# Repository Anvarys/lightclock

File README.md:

<div align="center">
  
</div>

<h2 align="center">Light Clock</h2>
<p align="center">
A custom PCB-based Clock/Alarm with a runrise alarm, a circle of capacitive touch controls to easily choose the time and a 2.42" OLED display
</p>

## About the project

A custom PCB-based Clock/Alarm with a 3d printed enclosure. It features a runrise alarm option (72 LEDs), a 2.42" OLED display, many capacitive touch controls (24 around in a circle and 4 for the main controls) and a buzzer.

I made this project because I wanted to have a runrise alarm to wake up more naturally and also be easy to set up alarms with few clicks and without any additional installation required.

## Light Clock's features in more detail

### Sunrise alarm & LEDs

Light Clock has a runsrise type of alarm, which will slowly rise the luminosity up to a set time for you to wake up naturally, like with a real sunrise. This can be calibrated, meaning you can set up a test alarm on a day you don't need to wake up at a certain time and see at which luminosity you will wake up. There is also a buzzer (the shaky circle on the simplified design picture) to wake you up with it, just in case, as you might not wake up from the light.

It uses 72LEDs with 3000K warm lighting, with a total maximum luminosity flux of over 2000 lumens. They can also be lighten up in individual groups of 3, so a total of 24 groups is present, to show the current time using those same LEDs but dimmed, also as it has 24 groups it can do both 24 and 12 sections for the time, which you can choose as you prefer.

### Capacitive touch controls

This project has a total of 28 capacitive touch sensors (you can identify all of them on the simplified design picture as the ones having unclear borders), they were made by placing pads on the PCB and using ICs to measure precise capacitance values. 

4 of them are used to control the menu: 2 arrows for navigating between options and change values, a circle to select an option and a square be used as a return button.

And the other 24 are distributed evenly in a circle next to the LEDs, they will be used to easily choose time of your alarm or change number variables. For example if you need to setup an alarm for 10:15am you can simply click the 10th pad counting clockwise from the top to set the hour, and then click on 7th pad to set the minutes.

### Display

The display is a 2.42" OLED display from Waveshare. It has a resolution of 128x64, which is not detailed, but very sufficent for pixeled fonts and interfaces. It will display the time in the format you prefer, and it can be set into a "show on touch" mode, so that the display would be off by default but when you touch any capacitive touch sensor it will show the time for a certain period of time.

### Other

It also has an RTC clock with a coin battery to sustain precise time for months, while the battery is not required it is very recommended as then if you power off the clock you won't need to set up the time again each time.

Since the LEDs and ICs produce heat there is a 40x40x7mm fan on the back which is very quiet, so should not be a worry that it might be disturbing.

Also I added 4 exposed GPIO pads on the PCB that you can use them to integrate something extra to this device if you want to.

## How to build your own light clock

First you would want to buy all the required components found in the [BOM](https://github.com/Anvarys/lightclock/blob/main/BOM/BOM.csv), order the pcb using the gerbers from the [production folder](https://github.com/Anvarys/lightclock/tree/main/PCB/production) (you can also find the positions file which is required for JLCPCB to solder components for you, which is also an option). Then you will need to solder everything by looking at the [schematic](https://github.com/Anvarys/lightclock/blob/main/images/schematic.pdf) for references of the components. Also you will need to 3d print the enclosure, files of which you can find in the [CAD folder](https://github.com/Anvarys/lightclock/tree/main/CAD). Now you will need to flash the device with the [firmware](https://github.com/Anvarys/lightclock/tree/main/firmware) using [VS code](https://code.visualstudio.com) with [PlatformIO](https://platformio.org). Then when you check that it boots up successfully you can assemble the enclosure by first mounting the fan on the back enclosure part, then mounting the pcb to it as well, and finally snap the front enclosure part on the PCB.

## Schematic

## PCB

3D renders:

<table><tr>
<td></td>
<td></td>
</tr></table>

## Assembly

## Assembled

<table><tr>
<td></td>
<td></td>
</tr></table>

## Tools I used

<ul style="list-style-type:none;">
  <li>PCB design: <a href="https://kicad.org">KiCAD</a></li>
  <li>3D design: <a href="https://www.autodesk.com/products/fusion-360/overview">Autodesk Fusion</a> (free version)</li>
  <li>Firmware: <a href="https://code.visualstudio.com">VS code</a> with <a href="https://platformio.org">PlatformIO</a></li>
  <li>Art: <a href="https://figma.com">Figma</a></li>
</ul>

## BOM

Totals
| | |
|-|-|
|Parts|102.84$|
|Supplies|22.08$|
|Shipping|39.34$|
|Everything|164.26$|

You can find the detailed BOM in [/BOM](https://github.com/Anvarys/lightclock/tree/main/BOM)

P.S. I had to choose fast shipping or amazon instead of aliexpress as otherwise I won't be able to build the project until August

## Repository structure

- [/CAD](https://github.com/Anvarys/lightclock/tree/main/CAD) - All the 3d models and the assembly
- [/PCB](https://github.com/Anvarys/lightclock/tree/main/PCB) - KiCAD PCB project
  - [/production](https://github.com/Anvarys/lightclock/tree/main/PCB/production) - Files required to produce the PCB (and PCBA for JLCPCB)
  - [/scripts](https://github.com/Anvarys/lightclock/tree/main/PCB/scripts) - Scripts I made in python to place the LEDs and capacitive touch pad footprints perfectly on the PCB
- [/firmware](https://github.com/Anvarys/lightclock/tree/main/firmware) - PlatformIO project with all firmware sources and configs
- [/BOM](https://github.com/Anvarys/lightclock/tree/main/BOM) - Bill of materials (the list of all parts you need to buy)
- [/images](https://github.com/Anvarys/lightclock/tree/main/images) - Images of the project such as 3d renders, schematic, PCB, zine, etc.

## Zine

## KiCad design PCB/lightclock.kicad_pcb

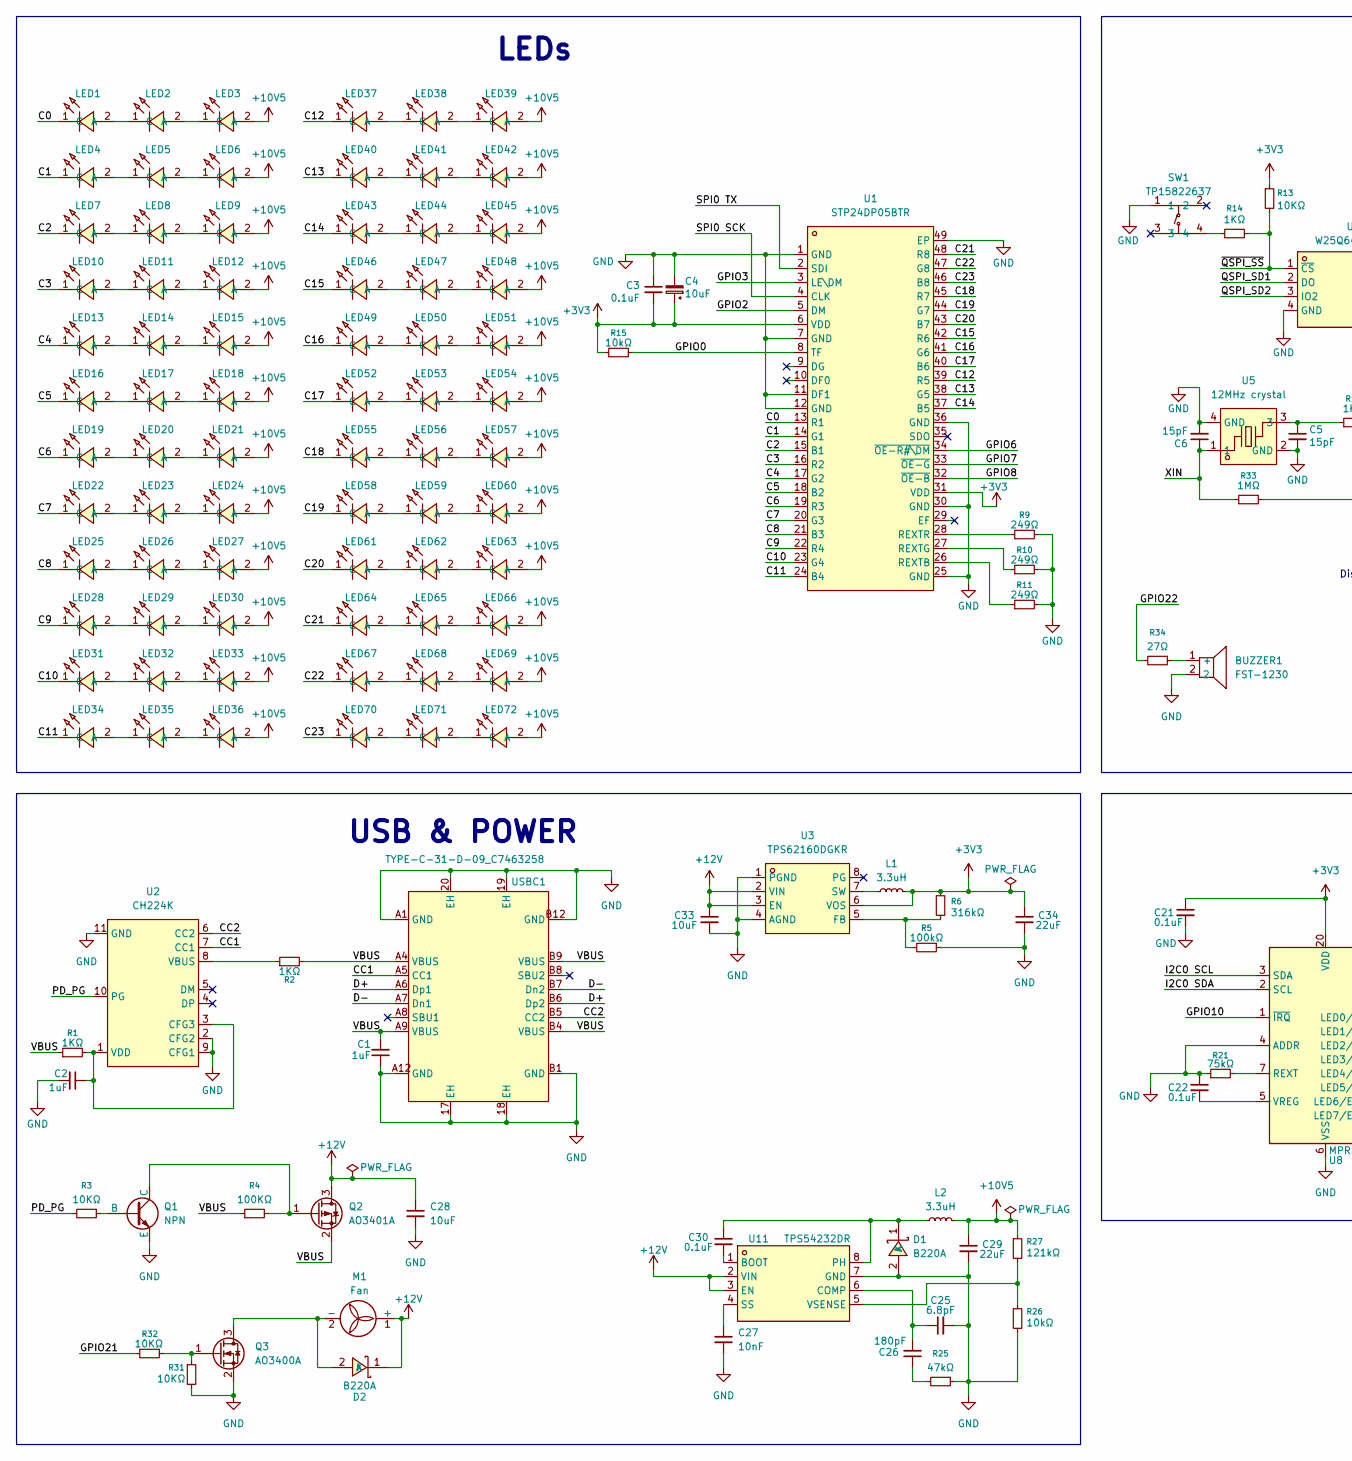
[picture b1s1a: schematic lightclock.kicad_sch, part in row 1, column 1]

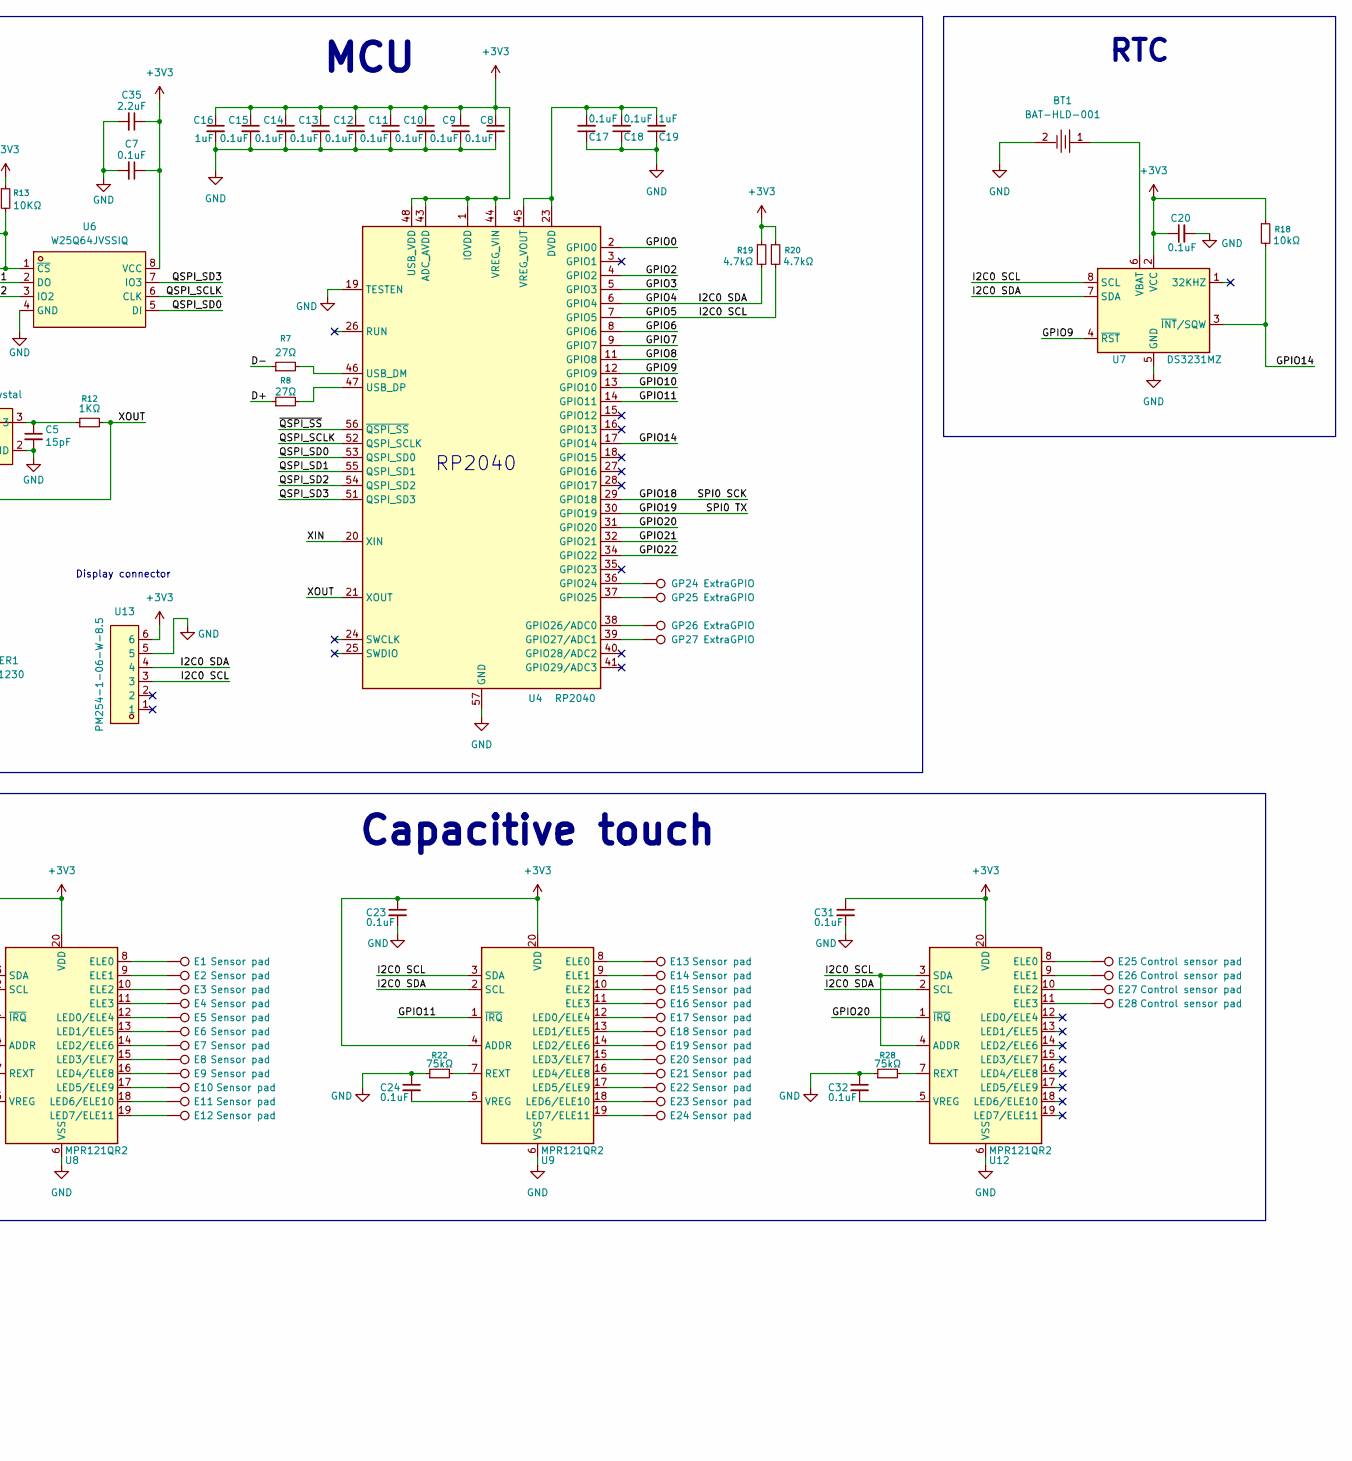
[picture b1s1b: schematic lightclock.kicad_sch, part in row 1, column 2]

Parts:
BT1: BAT-HLD-001; BAT-SMD_BAT-HLD-001; MPN BAT-HLD-001; LCSC Part C7501066
BUZZER1: FST-1230; BUZ-SMD_L12.0-W12.0_FUET-1230; MPN FUET-1230; LCSC Part C391037
C1, C2, C16, C19: 1uF; C0603
C3, C7, C8, C9, C10, C11, C12, C13, C14, C15, C17, C18, C20, C21, C22, C23, C24, C30, C31, C32: 0.1uF; C0603
C4, C28, C33: 10uF; C1206
C5, C6: 15pF; C0603
C25: 6.8pF; C0603
C26: 180pF; C0603
C27: 10nF; C0603
C29, C34: 22uF; C0805
C35: 2.2uF; C0805
D1, D2: B220A; SMA_L4.4-W2.8-LS5.4-RD; MPN B220A-13-F; LCSC Part C110481
E1, E2, E3, E4, E5, E6, E7, E8, E9, E10, E11, E12, E13, E14, E15, E16, E17, E18, E19, E20, E21, E22, E23, E24: Sensor pad; capacitive-touch-pad-trapezoid
E25, E26, E27, E28: Control sensor pad; capacitive-touch-pad-square10mm
GP24, GP25, GP26, GP27: ExtraGPIO; TestPoint_THTPad_1.5x1.5mm_Drill0.7mm
L1, L2: 3.3uH; IND-SMD_L7.0-W6.6
LED1, LED2, LED3, LED4, LED5, LED6, LED7, LED8, LED9, LED10, LED11, LED12, LED13, LED14, LED15, LED16, LED17, LED18, LED19, LED20, LED21, LED22, LED23, LED24, LED25, LED26, LED27, LED28, LED29, LED30, LED31, LED32, LED33, LED34, LED35, LED36, LED37, LED38, LED39, LED40, LED41, LED42, LED43, LED44, LED45, LED46, LED47, LED48, LED49, LED50, LED51, LED52, LED53, LED54, LED55, LED56, LED57, LED58, LED59, LED60, LED61, LED62, LED63, LED64, LED65, LED66, LED67, LED68, LED69, LED70, LED71, LED72: GW JTLMS1.EM-GVH3-XX57-1-60-R33; LED-SMD_L3.5-W2.8-RD_GW-JTLRS1.EM-K5L4-XX57-1; MPN GW JTLMS1.EM-GVH3-XX57-1-60-R33; LCSC Part C17215415
M1: Fan; SMD_2pads_polar_4mm_square
Q1: NPN; SOT-23-3_L2.9-W1.3-P1.90-LS2.4-BR
Q2: AO3401A; SOT-23
Q3: AO3400A; SOT-23
R1, R2: 1KΩ; R1210
R3, R13, R31, R32: 10KΩ; R0603
R4: 100KΩ; R0603
R5: 100kΩ; R0603
R6: 316kΩ; R0603
R7, R8, R34: 27Ω; R0603
R9, R10, R11: 249Ω; R1206
R12, R14: 1KΩ; R0603
R15, R18, R26: 10kΩ; R0603
R19, R20: 4.7kΩ; R0603
R21, R22, R28: 75kΩ; R0603
R25: 47kΩ; R0603
R27: 121kΩ; R0603
R33: 1MΩ; R0603
SW1: TP15822637; SW-SMD_4P-L5.2-W5.2-P3.70-LS6.4; MPN TP15822637; LCSC Part C49140441
U1: STP24DP05BTR; TQFP-48_L7.0-W7.0-P0.50-LS9.0-BL-EP3.5; MPN STP24DP05BTR; LCSC Part C157417
U2: CH224K; ESSOP-10_L4.9-W3.9-P1.0-LS6.0-TL-EP; MPN CH224K; LCSC Part C970725
U3: TPS62160DGKR; MSOP-8_L3.0-W3.0-P0.65-LS5.0-BL; MPN TPS62160DGKR; LCSC Part C60726
U4: RP2040; QFN-56-1EP_7x7mm_P0.4mm_EP3.2x3.2mm
U5: 12MHz crystal; CRYSTAL-SMD_4P-L3.2-W2.5-BL; MPN SX3B12.000F1210F30; LCSC Part C2901650
U6: W25Q64JVSSIQ; SOP-8_L5.3-W5.3-P1.27-LS8.0-BL; MPN W25Q64JVSSIQ; LCSC Part C83140
U7: DS3231MZ; SOIC-8_3.9x4.9mm_P1.27mm
U8, U9, U12: MPR121QR2; QFN-20_L3.0-W3.0-P0.40-BL
U11: TPS54232DR; SOIC-8_L4.9-W3.9-P1.27-LS6.0-BL; MPN TPS54232DR; LCSC Part C52653
U13: PM254-1-06-W-8.5; HDR-TH_6P-P2.54-H-F-W10.0-N; MPN PM254-1-06-W-8.5; LCSC Part C2897388
USBC1: TYPE-C-31-D-09_C7463258; USB-C-TH_TYPE-C-31-D-09; MPN TYPE-C-31-D-09; LCSC Part C7463258

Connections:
+3V3: C3.2, C4.1, C7.1, C8.1, C9.1, C10.1, C11.1, C12.1, C13.1, C14.1, C15.1, C16.1, C20.1, C21.1, C23.1, C31.1, C34.1, C35.1, L1.2, R6.1, R13.1, R15.1, R18.1, R19.1, R20.1, U1.6 (VDD), U1.31 (VDD), U3.6 (VOS), U4.1 (IOVDD), U4.10 (IOVDD), U4.22 (IOVDD), U4.33 (IOVDD), U4.42 (IOVDD), U4.43 (ADC_AVDD), U4.44 (VREG_VIN), U4.48 (USB_VDD), U4.49 (IOVDD), U6.8 (VCC), U7.2 (VCC), U8.20 (VDD), U9.4 (ADDR), U9.20 (VDD), U12.20 (VDD), U13.6
+10V5: C29.1, L2.2, LED3.2 (A), LED6.2 (A), LED9.2 (A), LED12.2 (A), LED15.2 (A), LED18.2 (A), LED21.2 (A), LED24.2 (A), LED27.2 (A), LED30.2 (A), LED33.2 (A), LED36.2 (A), LED39.2 (A), LED42.2 (A), LED45.2 (A), LED48.2 (A), LED51.2 (A), LED54.2 (A), LED57.2 (A), LED60.2 (A), LED63.2 (A), LED66.2 (A), LED69.2 (A), LED72.2 (A), R27.1
+12V: C28.1, C33.1, D2.1 (K), M1.1 (+), Q2.3 (D), U3.2 (VIN), U3.3 (EN), U11.2 (VIN), U11.3 (EN)
/C0: LED1.1 (C), U1.13 (R1)
/C1: LED4.1 (C), U1.14 (G1)
/C2: LED7.1 (C), U1.15 (B1)
/C3: LED10.1 (C), U1.16 (R2)
/C4: LED13.1 (C), U1.17 (G2)
/C5: LED16.1 (C), U1.18 (B2)
/C6: LED19.1 (C), U1.19 (R3)
/C7: LED22.1 (C), U1.20 (G3)
/C8: LED25.1 (C), U1.21 (B3)
/C9: LED28.1 (C), U1.22 (R4)
/C10: LED31.1 (C), U1.23 (G4)
/C11: LED34.1 (C), U1.24 (B4)
/C12: LED37.1 (C), U1.39 (R5)
/C13: LED40.1 (C), U1.38 (G5)
/C14: LED43.1 (C), U1.37 (B5)
/C15: LED46.1 (C), U1.42 (R6)
/C16: LED49.1 (C), U1.41 (G6)
/C17: LED52.1 (C), U1.40 (B6)
/C18: LED55.1 (C), U1.45 (R7)
/C19: LED58.1 (C), U1.44 (G7)
/C20: LED61.1 (C), U1.43 (B7)
/C21: LED64.1 (C), U1.48 (R8)
/C22: LED67.1 (C), U1.47 (G8)
/C23: LED70.1 (C), U1.46 (B8)
/CC1: U2.7 (CC1), USBC1.A5 (CC1)
/CC2: U2.6 (CC2), USBC1.B5 (CC2)
/D+: R8.1, USBC1.A6 (Dp1), USBC1.B6 (Dp2)
/D-: R7.1, USBC1.A7 (Dn1), USBC1.B7 (Dn2)
/GPIO0: R15.2, U1.8 (TF), U4.2 (GPIO0)
/GPIO2: U1.5 (DM), U4.4 (GPIO2)
/GPIO3: U1.3 (LE\DM), U4.5 (GPIO3)
/GPIO4: R19.2, U4.6 (GPIO4), U7.7 (SDA), U8.2 (SCL), U9.2 (SCL), U12.2 (SCL), U13.4
/GPIO5: R20.2, U4.7 (GPIO5), U7.8 (SCL), U8.3 (SDA), U9.3 (SDA), U12.3 (SDA), U12.4 (ADDR), U13.3
/GPIO6: U1.34 (~OE-R#\DM), U4.8 (GPIO6)
/GPIO7: U1.33 (~OE-G), U4.9 (GPIO7)
/GPIO8: U1.32 (~OE-B), U4.11 (GPIO8)
/GPIO9: U4.12 (GPIO9), U7.4 (~RST)
/GPIO10: U4.13 (GPIO10), U8.1 (~IRQ)
/GPIO11: U4.14 (GPIO11), U9.1 (~IRQ)
/GPIO14: R18.2, U4.17 (GPIO14), U7.3 (~INT/SQW)
/GPIO18: U1.4 (CLK), U4.29 (GPIO18)
/GPIO19: U1.2 (SDI), U4.30 (GPIO19)
/GPIO20: U4.31 (GPIO20), U12.1 (~IRQ)
/GPIO21: R32.2, U4.32 (GPIO21)
/GPIO22: R34.2, U4.34 (GPIO22)
/PD_PG: R3.2, U2.10 (PG)
/QSPI_SCLK: U4.52 (QSPI_SCLK), U6.6 (CLK)
/QSPI_SD0: U4.53 (QSPI_SD0), U6.5 (DI)
/QSPI_SD1: U4.55 (QSPI_SD1), U6.2 (DO)
/QSPI_SD2: U4.54 (QSPI_SD2), U6.3 (IO2)
/QSPI_SD3: U4.51 (QSPI_SD3), U6.7 (IO3)
/VBUS: C1.2, Q2.2 (S), R1.1, R2.2, R4.1, USBC1.A4 (VBUS), USBC1.A9 (VBUS), USBC1.B4 (VBUS), USBC1.B9 (VBUS)
/XIN: C6.1, R33.1, U4.20 (XIN), U5.1
/XOUT: R12.2, R33.2, U4.21 (XOUT)
/~QSPI_SS: R13.2, R14.2, U4.56 (~QSPI_SS), U6.1 (~CS)
GND: BT1.2, BUZZER1.2, C1.1, C2.2, C3.1, C4.2, C5.2, C6.2, C7.2, C8.2, C9.2, C10.2, C11.2, C12.2, C13.2, C14.2, C15.2, C16.2, C17.1, C18.1, C19.1, C20.2, C21.2, C22.1, C23.2, C24.1, C25.2, C27.2, C28.2, C29.2, C31.2, C32.1, C33.2, C34.2, C35.2, D1.2 (A), Q1.3 (E), Q3.2 (S), R5.1, R9.2, R10.2, R11.2, R21.1, R22.1, R25.1, R26.2, R28.1, R31.2, SW1.1, U1.1 (GND), U1.7 (GND), U1.11 (DF1), U1.12 (GND), U1.25 (GND), U1.30 (GND), U1.36 (GND), U1.49 (EP), U2.2 (CFG2), U2.9 (CFG1), U2.11 (GND), U3.1 (PGND), U3.4 (AGND), U4.19 (TESTEN), U4.57 (GND), U5.2 (GND), U5.4 (GND), U6.4 (GND), U7.5 (GND), U8.4 (ADDR), U8.6 (VSS), U9.6 (VSS), U11.7 (GND), U12.6 (VSS), U13.5, USBC1.17 (EH), USBC1.18 (EH), USBC1.19 (EH), USBC1.20 (EH), USBC1.A1 (GND), USBC1.A12 (GND), USBC1.B1 (GND), USBC1.B12 (GND)
unnamed: BUZZER1.1 (+), R34.1
unnamed: C5.1, R12.1, U5.3
unnamed: C26.1, R25.2
unnamed: C30.1, D1.1 (K), L2.1, U11.8 (PH)
unnamed: D2.2 (A), M1.2 (-), Q3.3 (D)
unnamed: LED1.2 (A), LED2.1 (C)
unnamed: LED2.2 (A), LED3.1 (C)
unnamed: LED4.2 (A), LED5.1 (C)
unnamed: LED5.2 (A), LED6.1 (C)
unnamed: LED7.2 (A), LED8.1 (C)
unnamed: LED8.2 (A), LED9.1 (C)
unnamed: LED10.2 (A), LED11.1 (C)
unnamed: LED11.2 (A), LED12.1 (C)
unnamed: LED13.2 (A), LED14.1 (C)
unnamed: LED14.2 (A), LED15.1 (C)
unnamed: LED16.2 (A), LED17.1 (C)
unnamed: LED17.2 (A), LED18.1 (C)
unnamed: LED19.2 (A), LED20.1 (C)
unnamed: LED20.2 (A), LED21.1 (C)
unnamed: LED22.2 (A), LED23.1 (C)
unnamed: LED23.2 (A), LED24.1 (C)
unnamed: LED25.2 (A), LED26.1 (C)
unnamed: LED26.2 (A), LED27.1 (C)
unnamed: LED28.2 (A), LED29.1 (C)
unnamed: LED29.2 (A), LED30.1 (C)
unnamed: LED31.2 (A), LED32.1 (C)
unnamed: LED32.2 (A), LED33.1 (C)
unnamed: LED34.2 (A), LED35.1 (C)
unnamed: LED35.2 (A), LED36.1 (C)
unnamed: LED37.2 (A), LED38.1 (C)
unnamed: LED38.2 (A), LED39.1 (C)
unnamed: LED40.2 (A), LED41.1 (C)
unnamed: LED41.2 (A), LED42.1 (C)
unnamed: LED43.2 (A), LED44.1 (C)
unnamed: LED44.2 (A), LED45.1 (C)
unnamed: LED46.2 (A), LED47.1 (C)
unnamed: LED47.2 (A), LED48.1 (C)
unnamed: LED49.2 (A), LED50.1 (C)
unnamed: LED50.2 (A), LED51.1 (C)
unnamed: LED52.2 (A), LED53.1 (C)
unnamed: LED53.2 (A), LED54.1 (C)
unnamed: LED55.2 (A), LED56.1 (C)
unnamed: LED56.2 (A), LED57.1 (C)
unnamed: LED58.2 (A), LED59.1 (C)
unnamed: LED59.2 (A), LED60.1 (C)
unnamed: LED61.2 (A), LED62.1 (C)
unnamed: LED62.2 (A), LED63.1 (C)
unnamed: LED64.2 (A), LED65.1 (C)
unnamed: LED65.2 (A), LED66.1 (C)
unnamed: LED67.2 (A), LED68.1 (C)
unnamed: LED68.2 (A), LED69.1 (C)
unnamed: LED70.2 (A), LED71.1 (C)
unnamed: LED71.2 (A), LED72.1 (C)
unnamed: Q1.2 (B), R3.1
unnamed: Q1.1 (C), Q2.1 (G), R4.2
unnamed: Q3.1 (G), R31.1, R32.1
unnamed: R14.1, SW1.4
unnamed: R11.1, U1.26 (REXTB)
unnamed: R10.1, U1.27 (REXTG)
unnamed: R9.1, U1.28 (REXTR)
unnamed: C2.1, R1.2, U2.1 (VDD), U2.3 (CFG3)
unnamed: R2.1, U2.8 (VBUS)
unnamed: R5.2, R6.2, U3.5 (FB)
unnamed: L1.1, U3.7 (SW)
unnamed: GP24.1 (1_1), U4.36 (GPIO24)
unnamed: GP25.1 (1_1), U4.37 (GPIO25)
unnamed: GP26.1 (1_1), U4.38 (GPIO26/ADC0)
unnamed: GP27.1 (1_1), U4.39 (GPIO27/ADC1)
unnamed: R7.2, U4.46 (USB_DM)
unnamed: R8.2, U4.47 (USB_DP)
unnamed: C17.2, C18.2, C19.2, U4.23 (DVDD), U4.45 (VREG_VOUT), U4.50 (DVDD)
unnamed: BT1.1, U7.6 (VBAT)
unnamed: E1.1 (1_1), U8.8 (ELE0)
unnamed: E2.1 (1_1), U8.9 (ELE1)
unnamed: E3.1 (1_1), U8.10 (ELE2)
unnamed: E4.1 (1_1), U8.11 (ELE3)
unnamed: E5.1 (1_1), U8.12 (LED0/ELE4)
unnamed: E6.1 (1_1), U8.13 (LED1/ELE5)
unnamed: E7.1 (1_1), U8.14 (LED2/ELE6)
unnamed: E8.1 (1_1), U8.15 (LED3/ELE7)
unnamed: E9.1 (1_1), U8.16 (LED4/ELE8)
unnamed: E10.1 (1_1), U8.17 (LED5/ELE9)
unnamed: E11.1 (1_1), U8.18 (LED6/ELE10)
unnamed: E12.1 (1_1), U8.19 (LED7/ELE11)
unnamed: R21.2, U8.7 (REXT)
unnamed: C22.2, U8.5 (VREG)
unnamed: E13.1 (1_1), U9.8 (ELE0)
unnamed: E14.1 (1_1), U9.9 (ELE1)
unnamed: E15.1 (1_1), U9.10 (ELE2)
unnamed: E16.1 (1_1), U9.11 (ELE3)
unnamed: E17.1 (1_1), U9.12 (LED0/ELE4)
unnamed: E18.1 (1_1), U9.13 (LED1/ELE5)
unnamed: E19.1 (1_1), U9.14 (LED2/ELE6)
unnamed: E20.1 (1_1), U9.15 (LED3/ELE7)
unnamed: E21.1 (1_1), U9.16 (LED4/ELE8)
unnamed: E22.1 (1_1), U9.17 (LED5/ELE9)
unnamed: E23.1 (1_1), U9.18 (LED6/ELE10)
unnamed: E24.1 (1_1), U9.19 (LED7/ELE11)
unnamed: R22.2, U9.7 (REXT)
unnamed: C24.2, U9.5 (VREG)
unnamed: C30.2, U11.1 (BOOT)
unnamed: C25.1, C26.2, U11.6 (COMP)
unnamed: C27.1, U11.4 (SS)
unnamed: R26.1, R27.2, U11.5 (VSENSE)
unnamed: E25.1 (1_1), U12.8 (ELE0)
unnamed: E26.1 (1_1), U12.9 (ELE1)
unnamed: E27.1 (1_1), U12.10 (ELE2)
unnamed: E28.1 (1_1), U12.11 (ELE3)
unnamed: R28.2, U12.7 (REXT)
unnamed: C32.2, U12.5 (VREG)

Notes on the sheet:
RP2040
RTC
MCU
Capacitive touch
LEDs
USB & POWER
Display connector

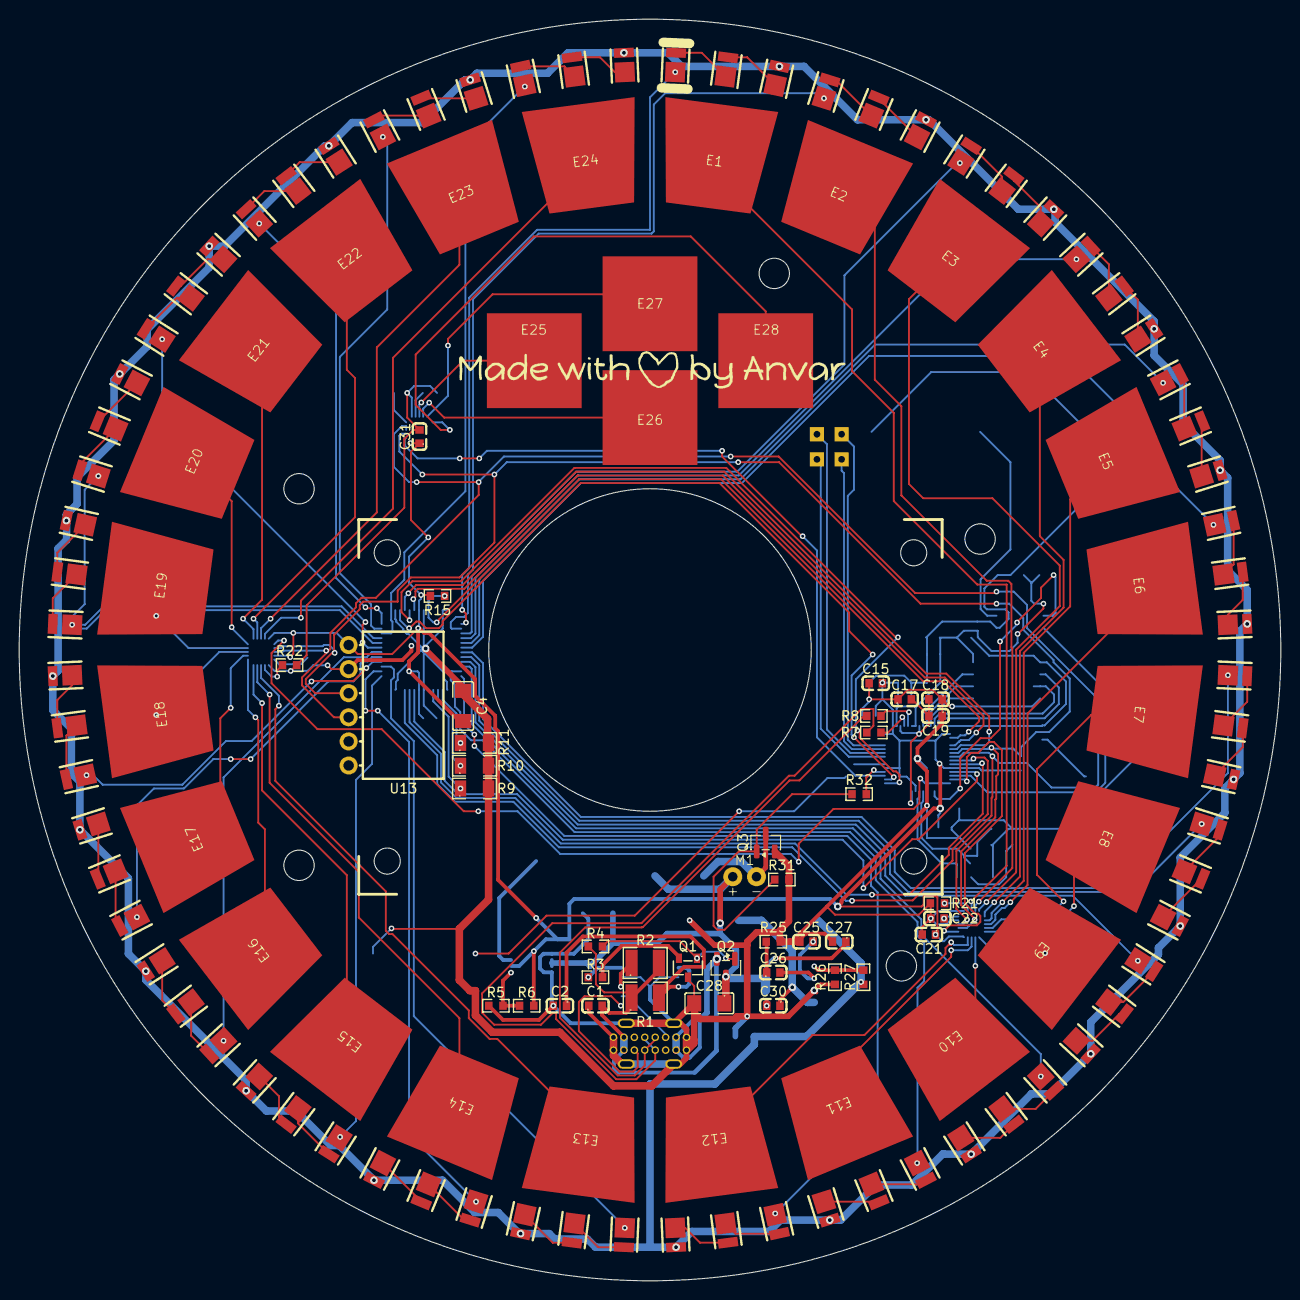
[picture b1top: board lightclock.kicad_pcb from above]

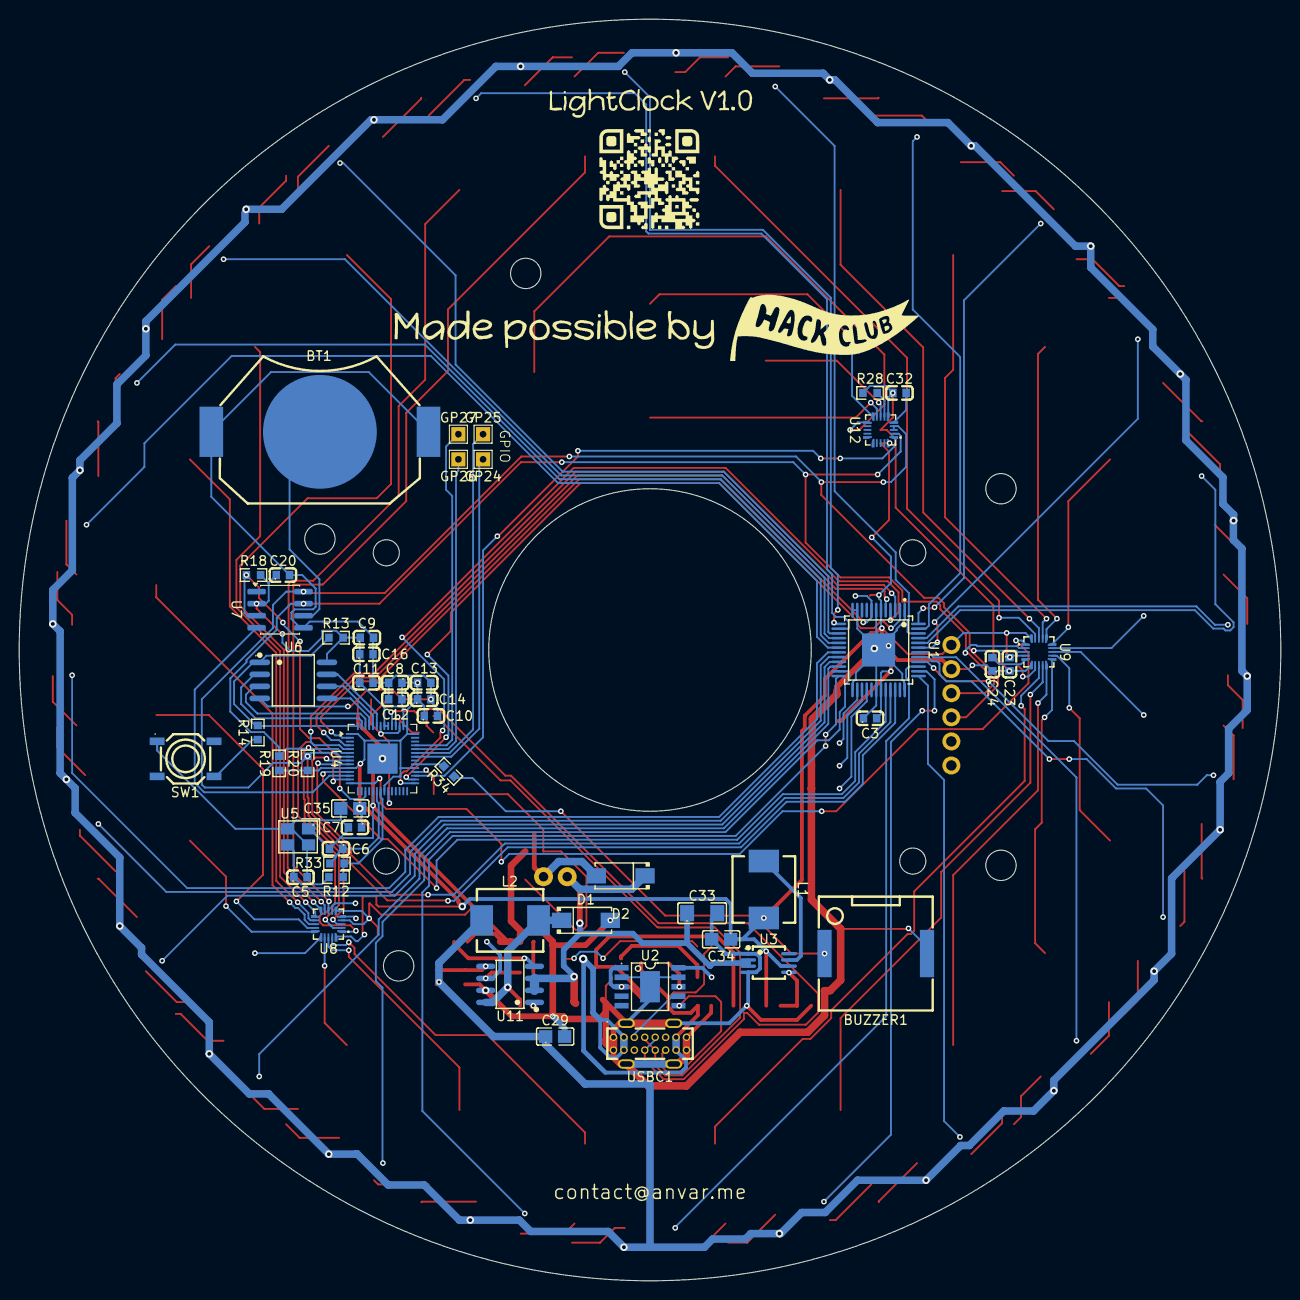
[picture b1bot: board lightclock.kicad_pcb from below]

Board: 2 copper layers, 133.0 x 133.0 mm, 191 parts (52 on the bottom side), 169 nets.

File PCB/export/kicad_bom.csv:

"Reference","Qty","Value","DNP","Exclude from BOM","Exclude from Board","Footprint","Datasheet"
"BT1","1","BAT-HLD-001","","","","easyeda2kicad:BAT-SMD_BAT-HLD-001","https://www.lcsc.com/datasheet/C7501066.pdf"
"BUZZER1","1","FST-1230","","","","easyeda2kicad:BUZ-SMD_L12.0-W12.0_FUET-1230","https://lcsc.com/product-detail/Buzzers_FST-FST-1230_C391037.html"
"C1,C2,C16,C19","4","1uF","","","","easyeda2kicad:C0603",""
"C3,C7,C8,C9,C10,C11,C12,C13,C14,C15,C17,C18,C20,C21,C22,C23,C24,C30,C31,C32","20","0.1uF","","","","easyeda2kicad:C0603",""
"C4,C28,C33","3","10uF","","","","easyeda2kicad:C1206",""
"C5,C6","2","15pF","","","","easyeda2kicad:C0603",""
"C25","1","6.8pF","","","","easyeda2kicad:C0603",""
"C26","1","180pF","","","","easyeda2kicad:C0603",""
"C27","1","10nF","","","","easyeda2kicad:C0603",""
"C29,C34","2","22uF","","","","easyeda2kicad:C0805",""
"C35","1","2.2uF","","","","easyeda2kicad:C0805",""
"D1","1","B220A","","","","easyeda2kicad:SMA_L4.4-W2.8-LS5.4-RD","https://lcsc.com/product-detail/Schottky-Barrier-Diodes-SBD_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"
"E1,E2,E3,E4,E5,E6,E7,E8,E9,E10,E11,E12,E13,E14,E15,E16,E17,E18,E19,E20,E21,E22,E23,E24","24","Sensor pad","","","","anvar:capacitive-touch-pad-trapezoid",""
"E25,E26,E27,E28","4","Control sensor pad","","","","anvar:capacitive-touch-pad-square10mm",""
"L1,L2","2","3.3uH","","","","easyeda2kicad:IND-SMD_L7.0-W6.6",""
"LED1,LED2,LED3,LED4,LED5,LED6,LED7,LED8,LED9,LED10,LED11,LED12,LED13,LED14,LED15,LED16,LED17,LED18,LED19,LED20,LED21,LED22,LED23,LED24,LED25,LED26,LED27,LED28,LED29,LED30,LED31,LED32,LED33,LED34,LED35,LED36,LED37,LED38,LED39,LED40,LED41,LED42,LED43,LED44,LED45,LED46,LED47,LED48,LED49,LED50,LED51,LED52,LED53,LED54,LED55,LED56,LED57,LED58,LED59,LED60,LED61,LED62,LED63,LED64,LED65,LED66,LED67,LED68,LED69,LED70,LED71,LED72","72","GW JTLMS1.EM-GVH3-XX57-1-60-R33","","","","easyeda2kicad:LED-SMD_L3.5-W2.8-RD_GW-JTLRS1.EM-K5L4-XX57-1","https://www.lcsc.com/datasheet/C17215415.pdf"
"M1","1","Fan","","","","anvar:SMD_2pads_polar_4mm_square",""
"Q1","1","NPN","","","","easyeda2kicad:SOT-23-3_L2.9-W1.3-P1.90-LS2.4-BR","https://ngspice.sourceforge.io/docs/ngspice-html-manual/manu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"
"Q2","1","AO3401A","","","","Package_TO_SOT_SMD:SOT-23","http://www.aosmd.com/pdfs/datasheet/AO3401A.pdf"
"Q3","1","AO3400A","","","","Package_TO_SOT_SMD:SOT-23","http://www.aosmd.com/pdfs/datasheet/AO3400A.pdf"
"R1,R2","2","1KΩ","","","","easyeda2kicad:R1210",""
"R3,R13,R31,R32","4","10KΩ","","","","easyeda2kicad:R0603",""
"R4","1","100KΩ","","","","easyeda2kicad:R0603",""
"R5","1","100kΩ","","","","easyeda2kicad:R0603",""
"R6","1","316kΩ","","","","easyeda2kicad:R0603",""
"R7,R8,R34","3","27Ω","","","","easyeda2kicad:R0603",""
"R9,R10,R11","3","249Ω","","","","easyeda2kicad:R1206",""
"R12,R14","2","1KΩ","","","","easyeda2kicad:R0603",""
"R15,R18,R26","3","10kΩ","","","","easyeda2kicad:R0603",""
"R19,R20","2","4.7kΩ","","","","easyeda2kicad:R0603",""
"R21,R22,R28","3","75kΩ","","","","easyeda2kicad:R0603",""
"R25","1","47kΩ","","","","easyeda2kicad:R0603",""
"R27","1","121kΩ","","","","easyeda2kicad:R0603",""
"R33","1","1MΩ","","","","easyeda2kicad:R0603",""
"SW1","1","TP15822637","","","","easyeda2kicad:SW-SMD_4P-L5.2-W5.2-P3.70-LS6.4","https://www.lcsc.com/datasheet/C49140441.pdf"
"U1","1","STP24DP05BTR","","","","easyeda2kicad:TQFP-48_L7.0-W7.0-P0.50-LS9.0-BL-EP3.5","https://www.lcsc.com/datasheet/C157417.pdf"
"U2","1","CH224K","","","","easyeda2kicad:ESSOP-10_L4.9-W3.9-P1.0-LS6.0-TL-EP","https://www.lcsc.com/datasheet/C970725.pdf"
"U3","1","TPS62160DGKR","","","","easyeda2kicad:MSOP-8_L3.0-W3.0-P0.65-LS5.0-BL","https://lcsc.com/product-detail/DC-DC-Converters_TI_TPS62160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"
"U4","1","RP2040","","","","Package_DFN_QFN:QFN-56-1EP_7x7mm_P0.4mm_EP3.2x3.2mm","https://datasheets.raspberrypi.com/rp2040/rp2040-datasheet.pdf"
"U5","1","12MHz crystal","","","","easyeda2kicad:CRYSTAL-SMD_4P-L3.2-W2.5-BL","https://www.lcsc.com/datasheet/C2901650.pdf"
"U6","1","W25Q64JVSSIQ","","","","easyeda2kicad:SOP-8_L5.3-W5.3-P1.27-LS8.0-BL","https://lcsc.com/product-detail/FLASH_W25Q64JVSSIQ_C83140.html"
"U7","1","DS3231MZ","","","","Package_SO:SOIC-8_3.9x4.9mm_P1.27mm","http://datasheets.maximintegrated.com/en/ds/DS3231M.pdf"
"U8,U9,U12","3","MPR121QR2","","","","easyeda2kicad:QFN-20_L3.0-W3.0-P0.40-BL","https://resurgentsemi.com/wp-content/uploads/2018/09/MPR121_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"
"U11","1","TPS54232DR","","","","easyeda2kicad:SOIC-8_L4.9-W3.9-P1.27-LS6.0-BL","https://lcsc.com/product-detail/DC-DC-Converters_TI_TPS54232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"
"U13","1","PM254-1-06-W-8.5","","","","easyeda2kicad:HDR-TH_6P-P2.54-H-F-W10.0-N","https://www.lcsc.com/datasheet/C2897388.pdf"
"USBC1","1","TYPE-C-31-D-09_C7463258","","","","easyeda2kicad:USB-C-TH_TYPE-C-31-D-09","https://www.lcsc.com/datasheet/C7463258.pdf"

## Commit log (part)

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2026-05-17 organised BOM
2026-05-19 added spare GPIO pads & ventilation for enclosure back
2026-05-21 added more CAD files & images
2026-05-21 updated BOM & images
2026-05-21 added README
2026-05-21 fix: remove bg of simplified_design
2026-05-22 updated README & added images
2026-05-22 fix: replaced jpeg images with png to have transparent bg
2026-05-22 modified coupled images to be in a row
2026-05-24 added firmware
2026-05-24 added RTC support to firmware & now it displays it
2026-05-24 added state management & control buttons handling
2026-05-24 connected INT pin on RTC to RP2040 for alarms
2026-05-25 added alarm
2026-05-25 added the zine
2026-05-25 updated PCB & schematic images
2026-05-25 updated BOM & added totals to README
2026-05-25 update production folder for PCB
2026-05-25 correct for warnings
2026-05-25 add a note about fast shipping
2026-05-30 updated BOM
2026-05-30 added 3d model to zine
